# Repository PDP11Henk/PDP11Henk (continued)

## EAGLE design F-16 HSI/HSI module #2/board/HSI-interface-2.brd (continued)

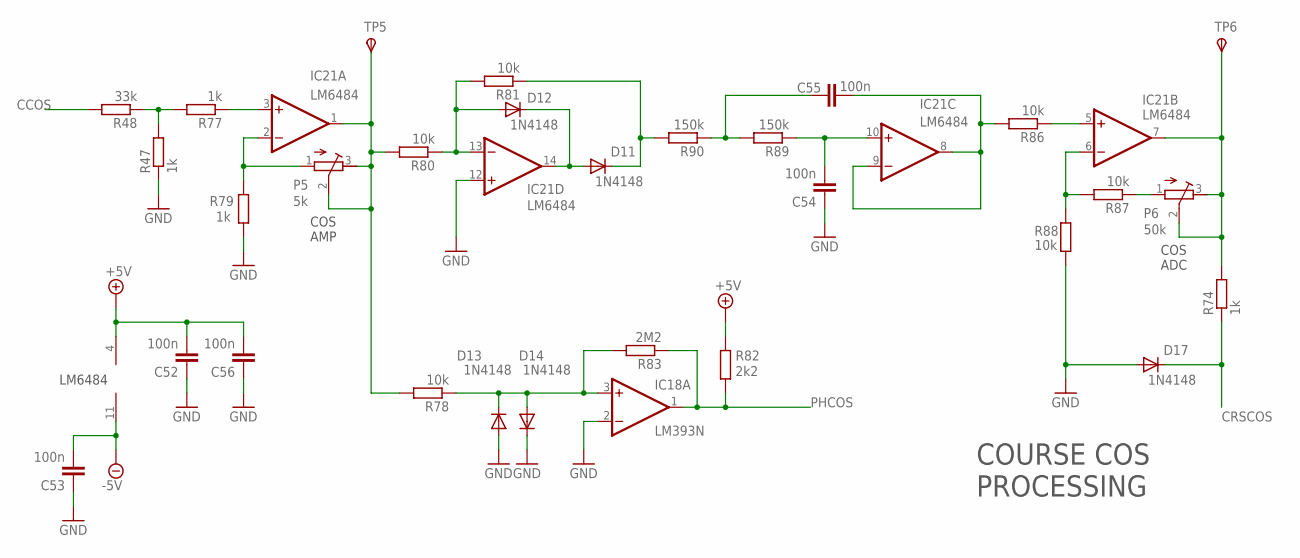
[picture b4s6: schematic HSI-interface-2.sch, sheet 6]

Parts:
C52, C53, C54, C55, C56: 100n; C025-025X050
D11, D12, D13, D14, D17: 1N4148; DO35-7
IC18: LM393N; DIL08
IC21: LM6484; DIL14
P5: 5k; RTRIM64Z
P6: 50k; RTRIM64Z
R47, R74, R77, R79: 1k; 0204/7
R48: 33k; 0204/7
R78, R80, R81, R86, R87, R88: 10k; 0204/7
R82: 2k2; 0204/7
R83: 2M2; 0204/7
R89, R90: 150k; 0204/7
TP5, TP6: TPSPAD1-13; P1-13

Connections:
+5V: C52.2, C56.2, IC21.4 (V+), R82.2; also elsewhere on the board
-5V: C53.2, IC21.11 (V-); also elsewhere on the board
CCOS: R48.2; also elsewhere on the board
CRSCOS: D17.C, R74.1; also elsewhere on the board
GND: C52.1, C53.1, C54.1, C56.1, D13.A, D14.C, D17.A, IC18.2 (-IN), IC21.12 (+IN), R47.1, R79.1, R88.2; also elsewhere on the board
unnamed: R47.2, R48.1, R77.2
unnamed: IC21.2 (-IN), P5.1 (E), R79.2
unnamed: IC21.1 (OUT), P5.2 (S), P5.3 (A), R78.2, R80.2, TP5.TP
unnamed: D11.A, D12.C, IC21.14 (OUT)
unnamed: D12.A, IC21.13 (-IN), R80.1, R81.2
unnamed: D11.C, R81.1, R90.2
unnamed: C55.1, R89.2, R90.1
unnamed: C54.2, IC21.10 (+IN), R89.1
unnamed: C55.2, IC21.8 (OUT), IC21.9 (-IN), R86.2
unnamed: IC21.5 (+IN), R86.1
unnamed: IC21.6 (-IN), R87.2, R88.1
unnamed: P6.1 (E), R87.1
unnamed: IC21.3 (+IN), R77.1
unnamed: D13.C, D14.A, IC18.3 (+IN), R78.1, R83.2
unnamed: IC21.7 (OUT), P6.2 (S), P6.3 (A), R74.2, TP6.TP
PHCOS: IC18.1 (OUT), R82.1, R83.1; also elsewhere on the board

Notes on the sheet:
LM6484
COS AMP
COS ADC
COURSE COS PROCESSING

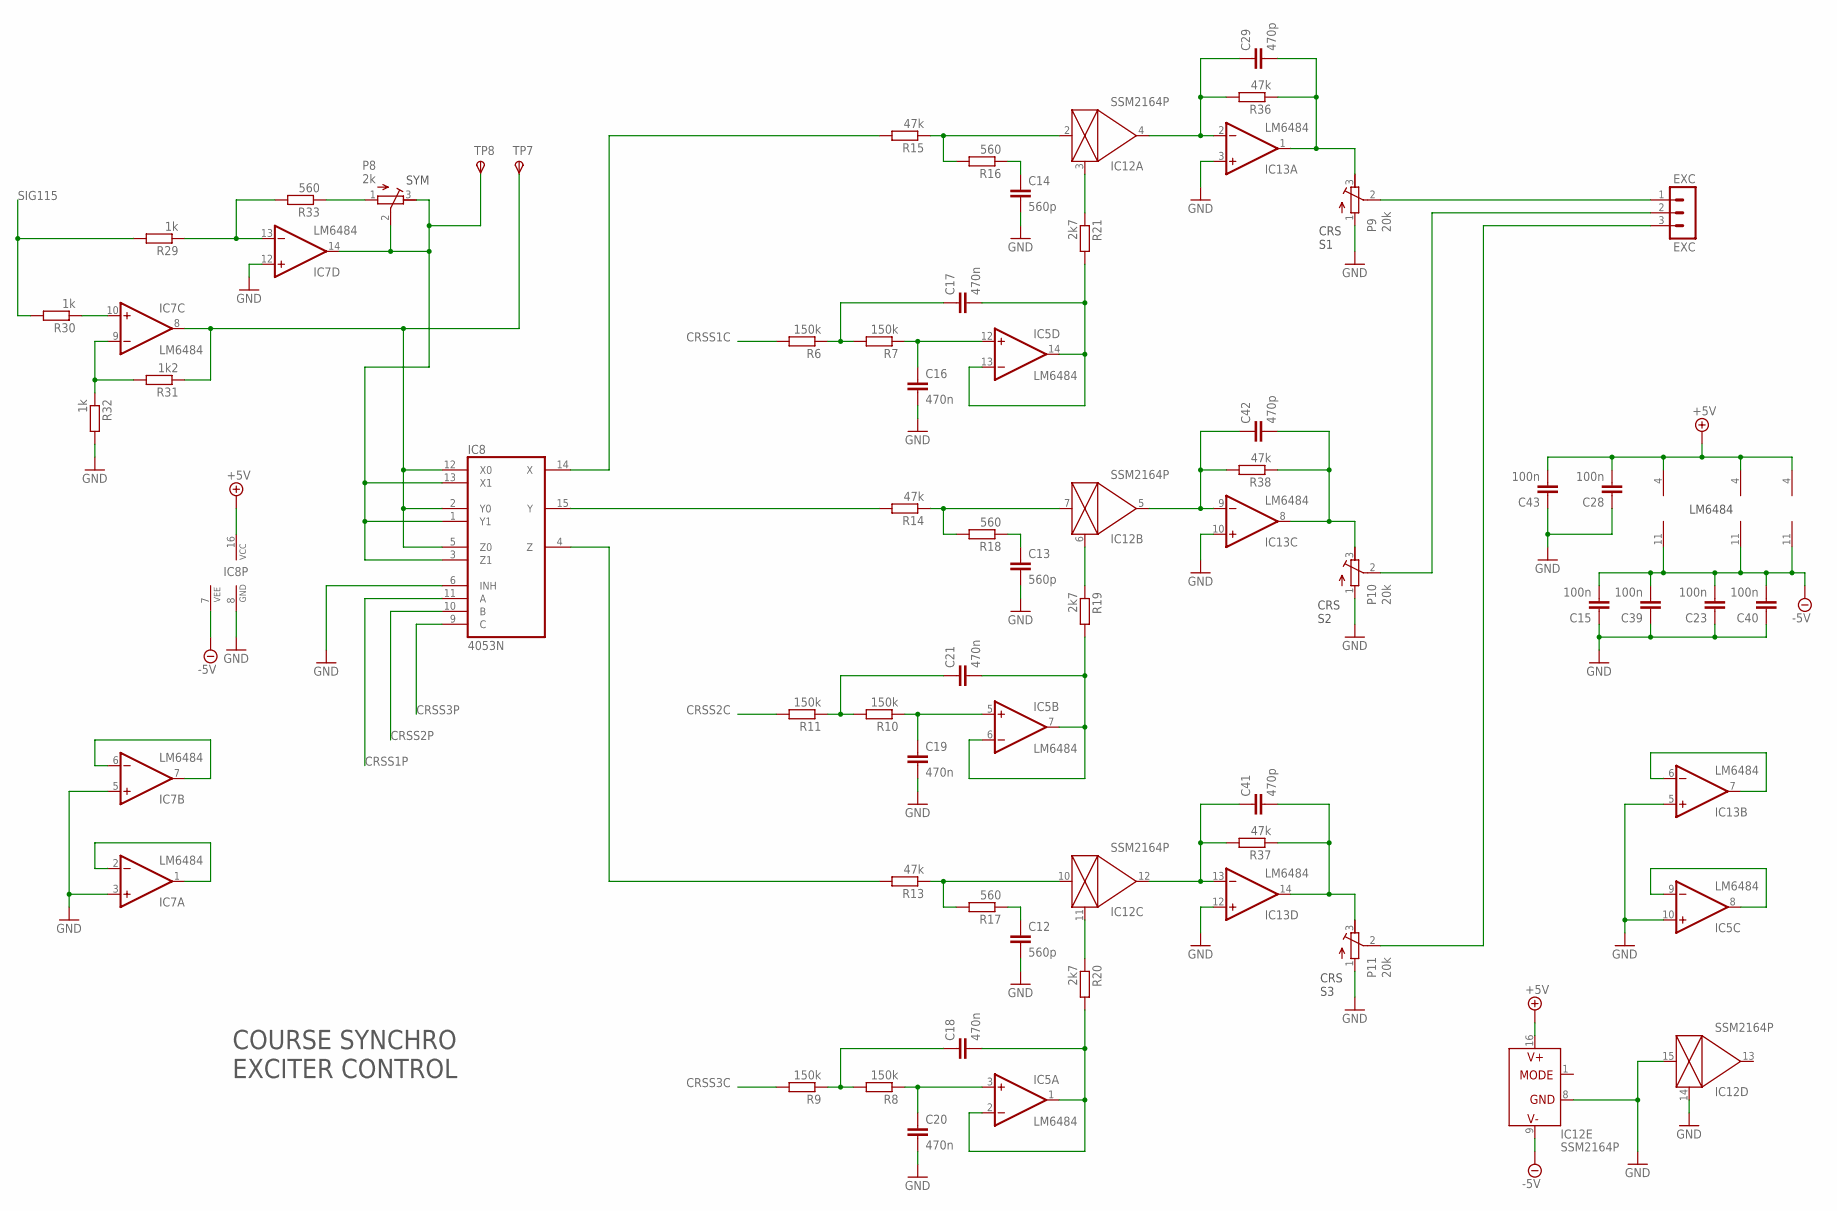
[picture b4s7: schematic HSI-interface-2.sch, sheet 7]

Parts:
C12, C13, C14: 560p; C025-025X050
C15, C23, C28, C39, C40, C43: 100n; C025-025X050
C16, C17, C18, C19, C20, C21: 470n; C025-025X050
C29, C41, C42: 470p; C025-025X050
EXC: EXC; MA03-1
IC5, IC7, IC13: LM6484; DIL14
IC8: 4053N; DIL16
IC12: SSM2164P; DIL16
P8: 2k; RTRIM64Z
P9, P10, P11: 20k; RTRIM64Z
R6, R7, R8, R9, R10, R11: 150k; 0204/7
R13, R14, R15, R36, R37, R38: 47k; 0204/7
R16, R17, R18, R33: 560; 0204/7
R19, R20, R21: 2k7; 0204/7
R29, R30, R32: 1k; 0204/7
R31: 1k2; 0204/7
TP7, TP8: TPSPAD1-13; P1-13

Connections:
+5V: C28.2, C43.2, IC5.4 (V+), IC7.4 (V+), IC8.16 (VCC), IC12.16 (V+), IC13.4 (V+); also elsewhere on the board
-5V: C15.2, C23.2, C39.2, C40.2, IC5.11 (V-), IC7.11 (V-), IC8.7 (VEE), IC12.9 (V-), IC13.11 (V-); also elsewhere on the board
CRSS1C: R6.2; also elsewhere on the board
CRSS1P: IC8.11 (A); also elsewhere on the board
CRSS2C: R11.2; also elsewhere on the board
CRSS2P: IC8.10 (B); also elsewhere on the board
CRSS3C: R9.2; also elsewhere on the board
CRSS3P: IC8.9 (C); also elsewhere on the board
GND: C12.2, C13.2, C14.2, C15.1, C16.2, C19.2, C20.2, C23.1, C28.1, C39.1, C40.1, C43.1, IC5.10 (+IN), IC7.3 (+IN), IC7.5 (+IN), IC7.12 (+IN), IC8.6 (INH), IC8.8 (GND), IC12.8 (GND), IC12.14 (CTRL), IC12.15 (IN), IC13.3 (+IN), IC13.5 (+IN), IC13.10 (+IN), IC13.12 (+IN), P9.1 (E), P10.1 (E), P11.1 (E), R32.2; also elsewhere on the board
unnamed: P8.1 (E), R33.1
unnamed: IC12.2 (IN), R15.1, R16.2
unnamed: C14.1, R16.1
unnamed: C29.1, IC12.4 (OUT), IC13.2 (-IN), R36.2
unnamed: C29.2, IC13.1 (OUT), P9.3 (A), R36.1
unnamed: C17.2, IC5.13 (-IN), IC5.14 (OUT), R21.2
unnamed: IC12.3 (CTRL), R21.1
unnamed: C16.1, IC5.12 (+IN), R7.1
unnamed: C17.1, R6.1, R7.2
unnamed: C42.1, IC12.5 (OUT), IC13.9 (-IN), R38.2
unnamed: C42.2, IC13.8 (OUT), P10.3 (A), R38.1
unnamed: IC12.6 (CTRL), R19.1
unnamed: IC12.7 (IN), R14.1, R18.2
unnamed: C13.1, R18.1
unnamed: C21.2, IC5.6 (-IN), IC5.7 (OUT), R19.2
unnamed: C21.1, R10.2, R11.1
unnamed: C19.1, IC5.5 (+IN), R10.1
unnamed: C41.1, IC12.12 (OUT), IC13.13 (-IN), R37.2
unnamed: C41.2, IC13.14 (OUT), P11.3 (A), R37.1
unnamed: IC12.10 (IN), R13.1, R17.2
unnamed: IC12.11 (CTRL), R20.1
unnamed: C12.1, R17.1
unnamed: C18.2, IC5.1 (OUT), IC5.2 (-IN), R20.2
unnamed: C18.1, R8.2, R9.1
unnamed: C20.1, IC5.3 (+IN), R8.1
unnamed: IC8.15 (Y), R14.2
unnamed: IC8.14 (X), R15.2
unnamed: IC8.4 (Z), R13.2
unnamed: IC7.1 (OUT), IC7.2 (-IN)
unnamed: IC7.13 (-IN), R29.1, R33.2
unnamed: IC7.9 (-IN), R31.2, R32.1
unnamed: IC7.8 (OUT), IC8.2 (Y0), IC8.5 (Z0), IC8.12 (X0), R31.1, TP7.TP
unnamed: IC7.14 (OUT), IC8.1 (Y1), IC8.3 (Z1), IC8.13 (X1), P8.2 (S), P8.3 (A), TP8.TP
unnamed: IC7.6 (-IN), IC7.7 (OUT)
unnamed: IC7.10 (+IN), R30.1
unnamed: IC13.6 (-IN), IC13.7 (OUT)
unnamed: IC5.8 (OUT), IC5.9 (-IN)
unnamed: EXC.1, P9.2 (S)
unnamed: EXC.2, P10.2 (S)
unnamed: EXC.3, P11.2 (S)
SIG115: R29.2, R30.2; also elsewhere on the board

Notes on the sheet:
LM6484
CRS S1
CRS S2
CRS S3
COURSE SYNCHRO EXCITER CONTROL
SYM

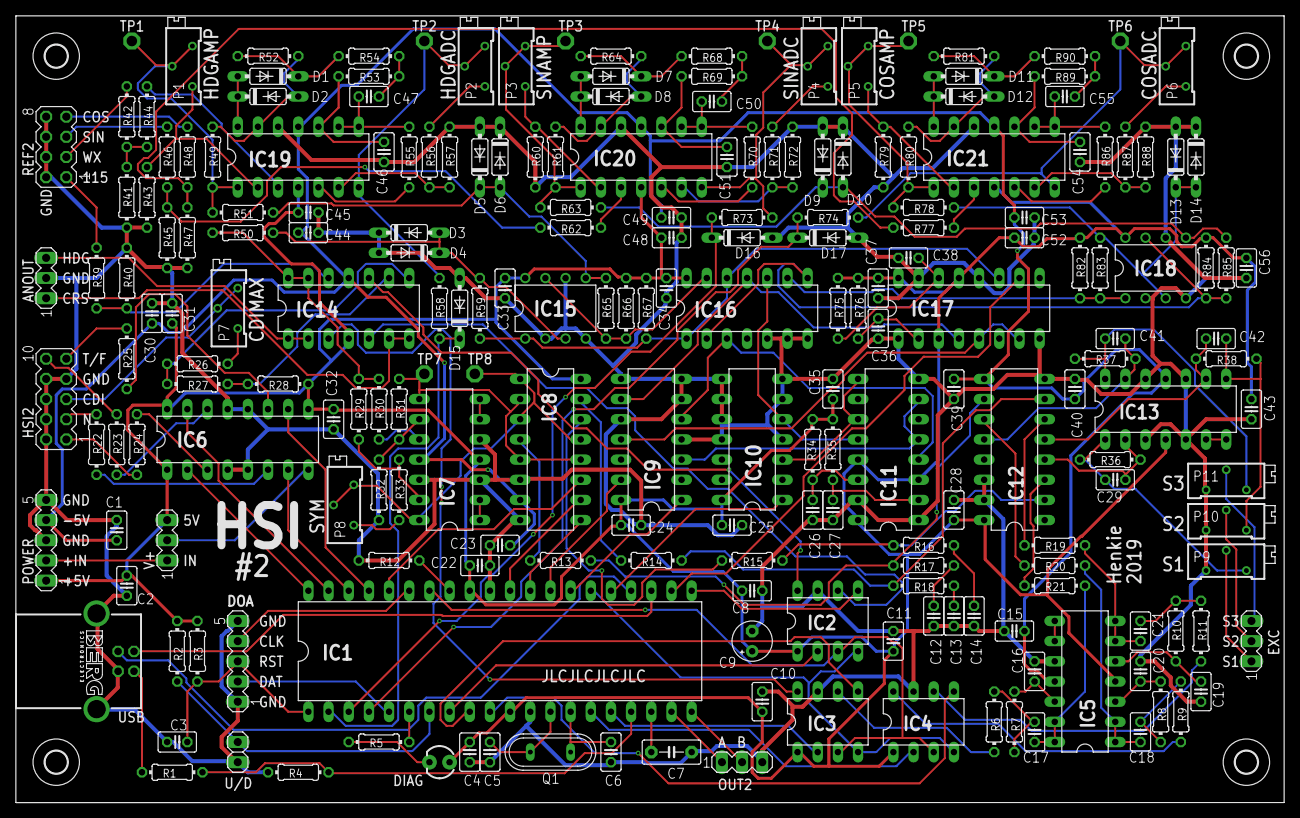
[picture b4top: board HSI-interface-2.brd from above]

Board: 2 copper layers, 159.7 x 99.1 mm, 219 parts (0 on the bottom side), 169 nets.

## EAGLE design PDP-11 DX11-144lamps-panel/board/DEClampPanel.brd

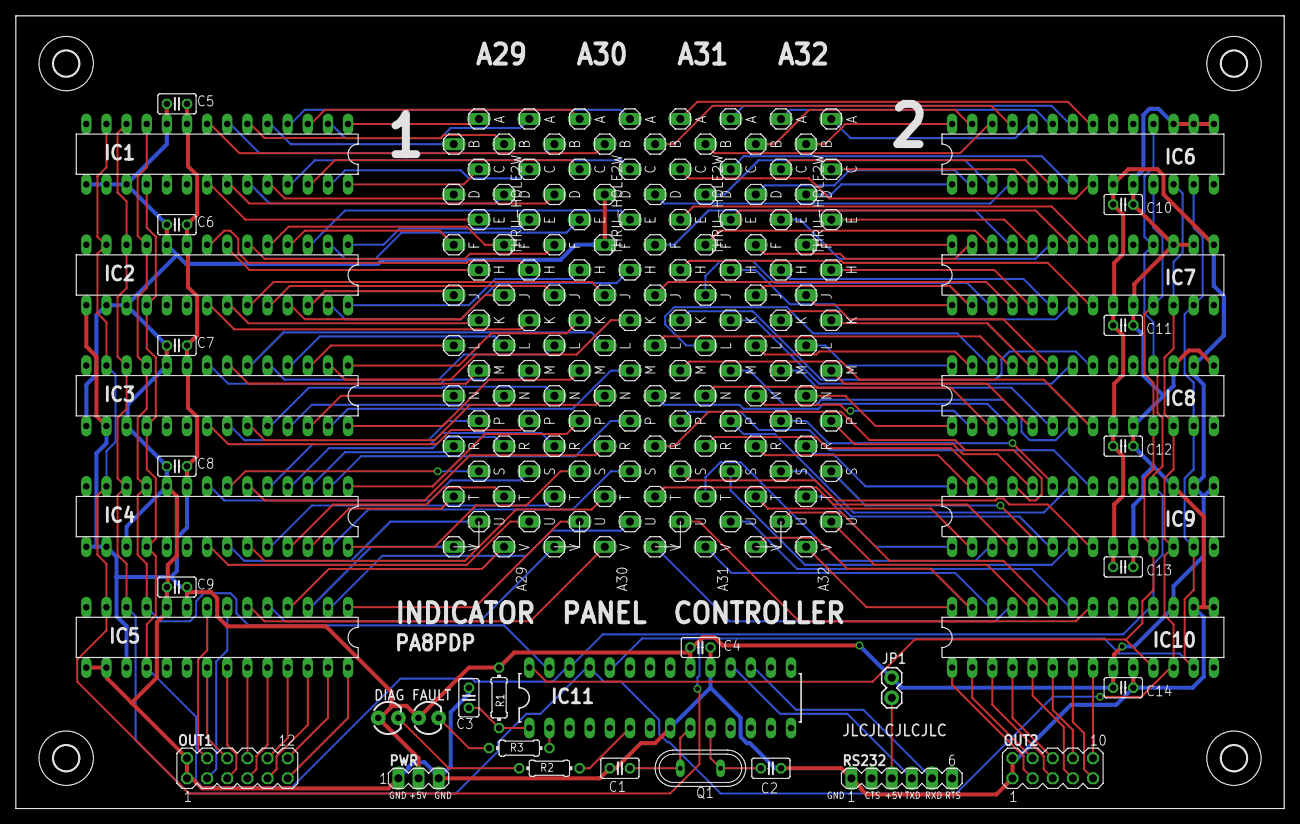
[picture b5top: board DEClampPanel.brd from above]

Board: 2 copper layers, 160.0 x 100.0 mm, 44 parts (0 on the bottom side), 177 nets.

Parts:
A29, A30, A31, A32: THRU-HOLE2W; THRU-HOLE2
C1, C2: 18pF; C025-025X050
C3, C4, C5, C6, C7, C8, C9, C10, C11, C12, C13, C14: 100nF; C025-025X050
DIAG: DIAG; LED3MM
FAULT: FAULT; LED3MM
H1, H2, H3, H4: MOUNT-HOLE3.2; 3,2
IC1, IC2, IC3, IC4, IC5, IC6, IC7, IC8, IC9, IC10: MCP23S17SP; DIL28-3
IC11: PIC18F2550; DIL28-3
JP1: JP1; 1X02
OUT1: OUT1; MA06-2
OUT2: OUT2; MA05-2
PWR: PWR; MA03-1
Q1: 10MHz; QS
R1: 10k; 0204/7
R2, R3: 470; 0204/7
RS232: RS232; MA06-1

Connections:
CS1: IC1.11, IC2.11, IC3.11, IC4.11, IC5.11, IC11.27
CS2: IC6.11, IC7.11, IC8.11, IC9.11, IC10.11, IC11.28
GND: A30.D2, A30.F2, C1.1, C2.1, C3.2, C4.2, C5.2, C6.2, C7.2, C8.2, C9.2, C10.2, C11.2, C12.2, C13.2, C14.2, IC1.10, IC1.15, IC1.16, IC1.17, IC2.10, IC2.16, IC2.17, IC3.10, IC3.15, IC3.17, IC4.10, IC4.17, IC5.10, IC5.15, IC5.16, IC6.10, IC6.15, IC6.16, IC6.17, IC7.10, IC7.16, IC7.17, IC8.10, IC8.15, IC8.17, IC9.10, IC9.17, IC10.10, IC10.15, IC10.16, IC11.8, IC11.19, OUT1.1, OUT1.2, OUT2.1, OUT2.2, PWR.1, PWR.3, RS232.1
unnamed: IC1.18, IC2.18, IC3.18, IC4.18, IC5.18, IC6.18, IC7.18, IC8.18, IC9.18, IC10.18, IC11.26
unnamed: C1.2, IC11.9, Q1.1
unnamed: IC1.12, IC2.12, IC3.12, IC4.12, IC5.12, IC6.12, IC7.12, IC8.12, IC9.12, IC10.12, IC11.25
unnamed: IC1.13, IC2.13, IC3.13, IC4.13, IC5.13, IC6.13, IC7.13, IC8.13, IC9.13, IC10.13, IC11.24
unnamed: FAULT.K, R3.2
unnamed: C2.2, IC11.10, Q1.2
unnamed: JP1.1, RS232.3
unnamed: IC11.18, RS232.4
unnamed: IC11.17, RS232.5
unnamed: IC11.2, R3.1
unnamed: C3.1, IC11.1, R1.1
unnamed: DIAG.K, R2.2
unnamed: IC11.6, R2.1
VDD: C4.1, C5.1, C6.1, C7.1, C8.1, C9.1, C10.1, C11.1, C12.1, C13.1, C14.1, DIAG.A, FAULT.A, IC1.9, IC2.9, IC2.15, IC3.9, IC3.16, IC4.9, IC4.15, IC4.16, IC5.9, IC5.17, IC6.9, IC7.9, IC7.15, IC8.9, IC8.16, IC9.9, IC9.15, IC9.16, IC10.9, IC10.17, IC11.20, JP1.2, PWR.2, R1.2
X000: A29.E1, IC1.21
X001: A30.D1, IC1.22
X002: A29.D2, IC1.23
X003: A29.D1, IC1.24
X004: A30.C2, IC1.25
X005: A30.C1, IC1.26
X006: A29.C2, IC1.27
X007: A29.C1, IC1.28
X008: A29.A1, IC1.1
X009: A29.A2, IC1.2
X010: A30.A1, IC1.3
X011: A30.A2, IC1.4
X012: A29.B1, IC1.5
X013: A29.B2, IC1.6
X014: A30.B1, IC1.7
X015: A30.B2, IC1.8
X016: A29.K2, IC2.21
X017: A29.K1, IC2.22
X018: A30.J2, IC2.23
X019: A30.J1, IC2.24
X020: A29.J2, IC2.25
X021: A29.J1, IC2.26
X022: A30.H2, IC2.27
X023: A30.H1, IC2.28
X024: A29.E2, IC2.1
X025: A30.E1, IC2.2
X026: A30.E2, IC2.3
X027: A29.F1, IC2.4
X028: A29.F2, IC2.5
X029: A30.F1, IC2.6
X030: A29.H1, IC2.7
X031: A29.H2, IC2.8
X032: A29.P2, IC3.21
X033: A29.P1, IC3.22
X034: A30.N2, IC3.23
X035: A30.N1, IC3.24
X036: A29.N2, IC3.25
X037: A29.N1, IC3.26
X038: A30.M2, IC3.27
X039: A30.M1, IC3.28
X040: A30.K1, IC3.1
X041: A30.K2, IC3.2
X042: A29.L1, IC3.3
X043: A29.L2, IC3.4
X044: A30.L1, IC3.5
X045: A30.L2, IC3.6
X046: A29.M1, IC3.7
X047: A29.M2, IC3.8
X048: A29.U2, IC4.21
X049: A29.U1, IC4.22
X050: A30.T2, IC4.23
X051: A30.T1, IC4.24
X052: A29.T2, IC4.25
X053: A29.T1, IC4.26
X054: A30.S2, IC4.27
X055: A30.S1, IC4.28
X056: A30.P1, IC4.1
X057: A30.P2, IC4.2
X058: A29.R1, IC4.3
X059: A29.R2, IC4.4
X060: A30.R1, IC4.5
X061: A30.R2, IC4.6
X062: A29.S1, IC4.7
X063: A29.S2, IC4.8
X064: IC5.21, OUT1.6
X065: IC5.22, OUT1.5
X066: IC5.23, OUT1.8
X067: IC5.24, OUT1.7
X068: IC5.25, OUT1.10
X069: IC5.26, OUT1.9
X070: IC5.27, OUT1.12
X071: IC5.28, OUT1.11
X072: A30.U1, IC5.1
X073: A30.U2, IC5.2
X074: A29.V1, IC5.3
X075: A29.V2, IC5.4
X076: A30.V1, IC5.5
X077: A30.V2, IC5.6
X078: IC5.7, OUT1.3
X079: IC5.8, OUT1.4
X080: A31.A1, IC6.21
X081: A31.A2, IC6.22
X082: A32.A1, IC6.23
X083: A32.A2, IC6.24
X084: A31.B1, IC6.25
X085: A31.B2, IC6.26
X086: A32.B1, IC6.27
X087: A32.B2, IC6.28
X088: A32.D2, IC6.1
X089: A32.D1, IC6.2
X090: A31.D2, IC6.3
X091: A31.D1, IC6.4
X092: A32.C2, IC6.5
X093: A32.C1, IC6.6
X094: A31.C2, IC6.7
X095: A31.C1, IC6.8
X096: A31.E1, IC7.21
X097: A31.E2, IC7.22
X098: A32.E1, IC7.23
X099: A32.E2, IC7.24
X100: A31.F1, IC7.25
X101: A31.F2, IC7.26
X102: A32.F1, IC7.27
X103: A32.F2, IC7.28
X104: A32.J2, IC7.1
X105: A32.J1, IC7.2
X106: A31.J2, IC7.3
X107: A31.J1, IC7.4
X108: A32.H2, IC7.5
X109: A32.H1, IC7.6
X110: A31.H2, IC7.7
X111: A31.H1, IC7.8
X112: A31.K1, IC8.21
X113: A31.K2, IC8.22
X114: A32.K1, IC8.23
X115: A32.K2, IC8.24
X116: A31.L1, IC8.25
X117: A31.L2, IC8.26
X118: A32.L1, IC8.27
X119: A32.L2, IC8.28
X120: A32.N2, IC8.1
X121: A32.N1, IC8.2
X122: A31.N2, IC8.3
X123: A31.N1, IC8.4
X124: A32.M2, IC8.5
X125: A32.M1, IC8.6
X126: A31.M2, IC8.7
X127: A31.M1, IC8.8
X128: A31.P1, IC9.21
X129: A31.P2, IC9.22
X130: A32.P1, IC9.23
X131: A32.P2, IC9.24
X132: A31.R1, IC9.25
X133: A31.R2, IC9.26
X134: A32.R1, IC9.27
X135: A32.R2, IC9.28
X136: A32.T2, IC9.1
X137: A32.T1, IC9.2
X138: A31.T2, IC9.3
X139: A31.T1, IC9.4
X140: A32.S2, IC9.5
X141: A32.S1, IC9.6
X142: A31.S2, IC9.7
X143: A31.S1, IC9.8
X144: A31.U1, IC10.21
X145: A31.U2, IC10.22
X146: A32.U1, IC10.23
X147: A32.U2, IC10.24
X148: A31.V1, IC10.25
X149: A31.V2, IC10.26
X150: A32.V1, IC10.27
X151: A32.V2, IC10.28
X152: IC10.1, OUT2.3
X153: IC10.2, OUT2.4
X154: IC10.3, OUT2.5
X155: IC10.4, OUT2.6
X156: IC10.5, OUT2.7
X157: IC10.6, OUT2.8
X158: IC10.7, OUT2.9
X159: IC10.8, OUT2.10
